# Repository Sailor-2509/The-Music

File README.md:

# The-Music
A Casio of 12 keys
I started by making a file known as Casio 
the i opened the scamatic editor and added the components
 
 Then with this symbol
 
I added the footprints

Then by this button I entered in the pcb editor
Then I had to convet The footprints editor components to pcb editor so i used this button
 after converting i aranged them And wired it Than i saw it in 3D view 
After that my PCB work was done then I started dusighing my 3D moddel now it was done i bacically made a base plate and extruded it  it was finally done:)

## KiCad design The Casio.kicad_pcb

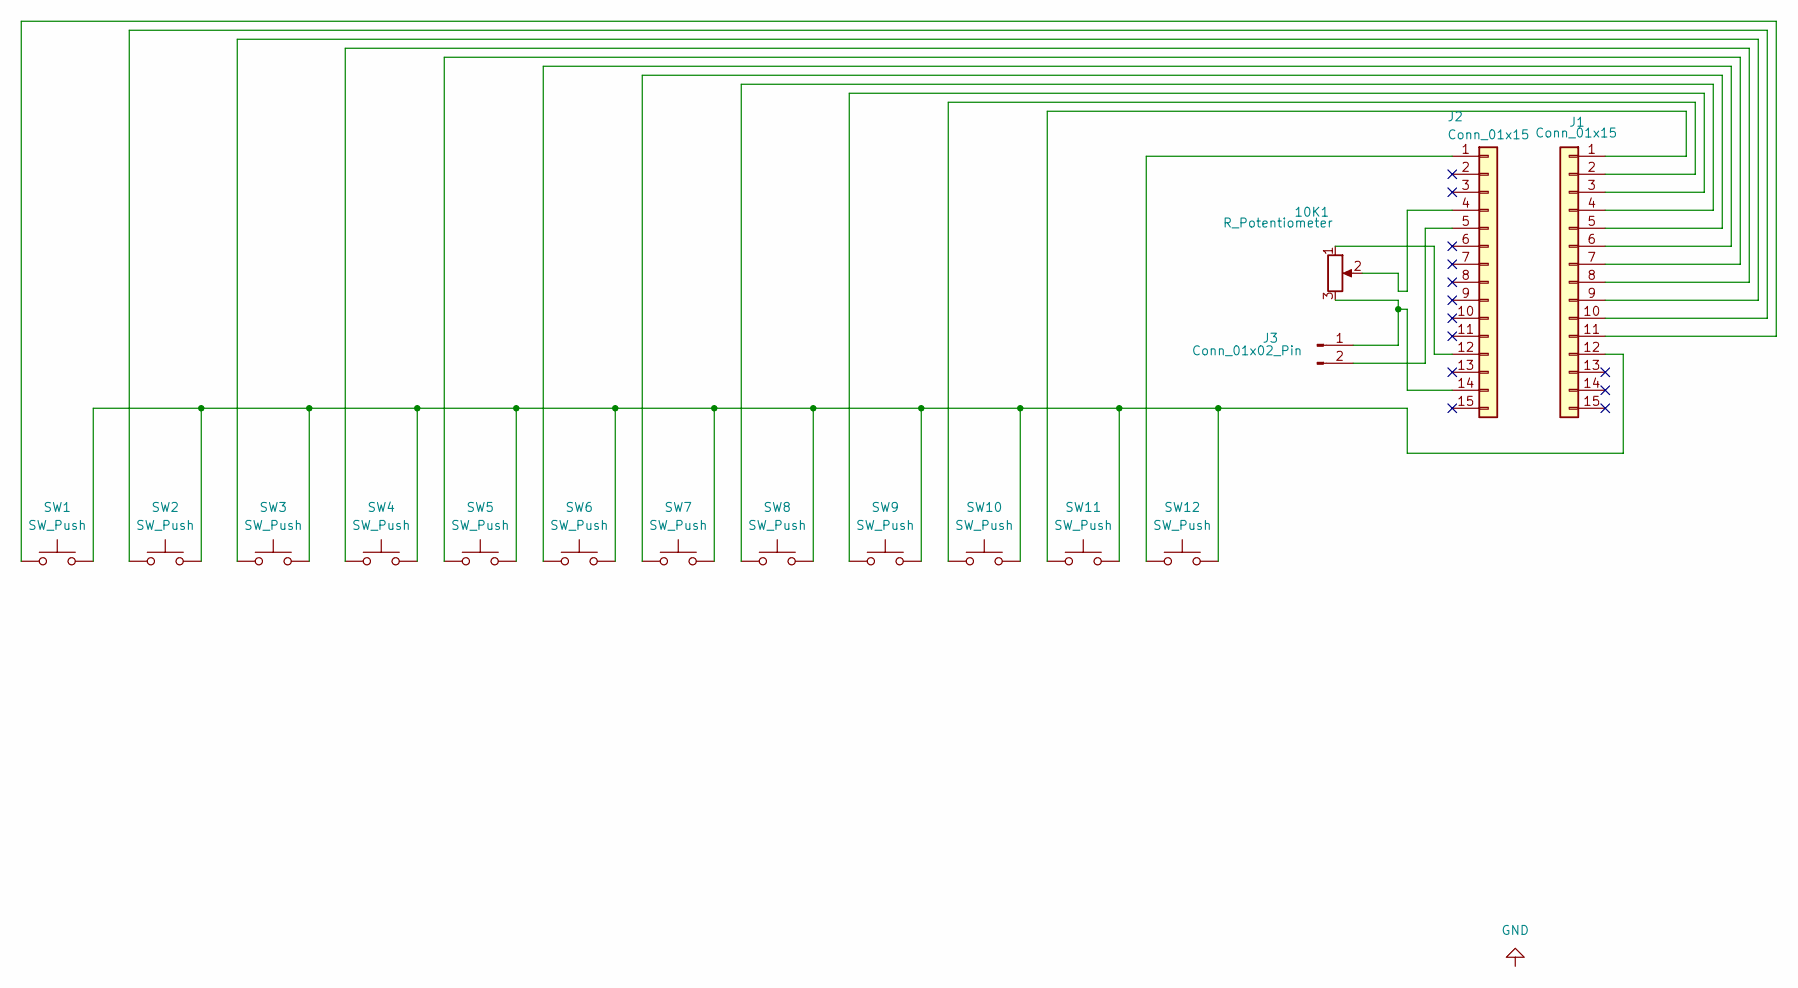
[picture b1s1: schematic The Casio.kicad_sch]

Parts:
10K1: R_Potentiometer; Potentiometer_Alps_RK163_Single_Horizontal
J1, J2: Conn_01x15; PinSocket_1x15_P2.00mm_Vertical
J3: Conn_01x02_Pin; PinSocket_1x02_P2.00mm_Vertical
SW1, SW2, SW3, SW4, SW5, SW6, SW7, SW8, SW9, SW10, SW11, SW12: SW_Push; SW_Cherry_MX_1.00u_PCB

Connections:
unnamed: J1.1, SW11.1
unnamed: J1.2, SW10.1
unnamed: J1.3, SW9.1
unnamed: J1.4, SW8.1
unnamed: J1.5, SW7.1
unnamed: J1.6, SW6.1
unnamed: J1.7, SW5.1
unnamed: J1.8, SW4.1
unnamed: J1.9, SW3.1
unnamed: J1.10, SW2.1
unnamed: J1.11, SW1.1
unnamed: J1.12, SW1.2, SW2.2, SW3.2, SW4.2, SW5.2, SW6.2, SW7.2, SW8.2, SW9.2, SW10.2, SW11.2, SW12.2
unnamed: J2.1, SW12.1
unnamed: 10K1.2, J2.4
unnamed: J2.5, J3.2
unnamed: 10K1.1, J2.12
unnamed: 10K1.3, J2.14, J3.1

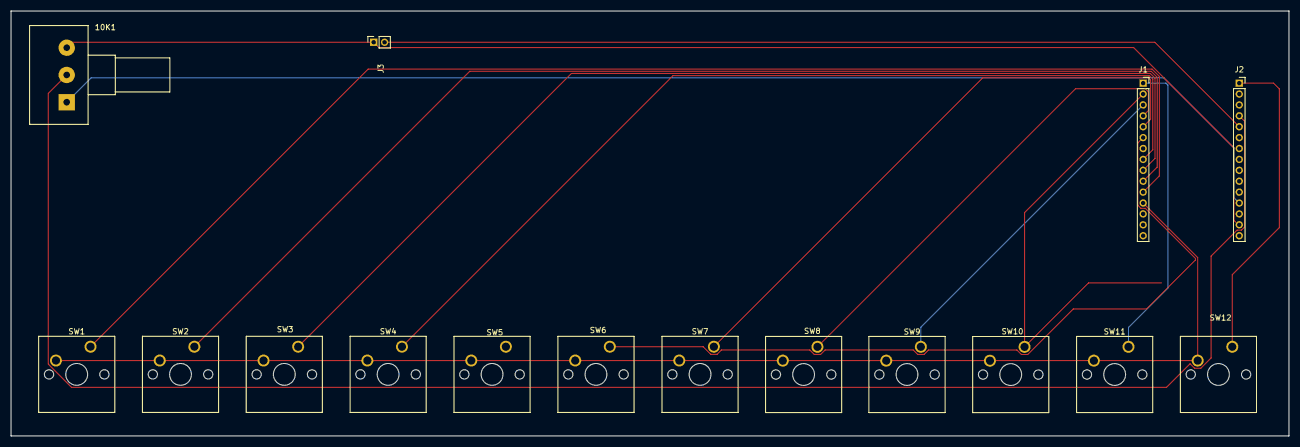
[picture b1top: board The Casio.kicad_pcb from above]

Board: 2 copper layers, 234.5 x 78.0 mm, 16 parts (0 on the bottom side), 17 nets.
